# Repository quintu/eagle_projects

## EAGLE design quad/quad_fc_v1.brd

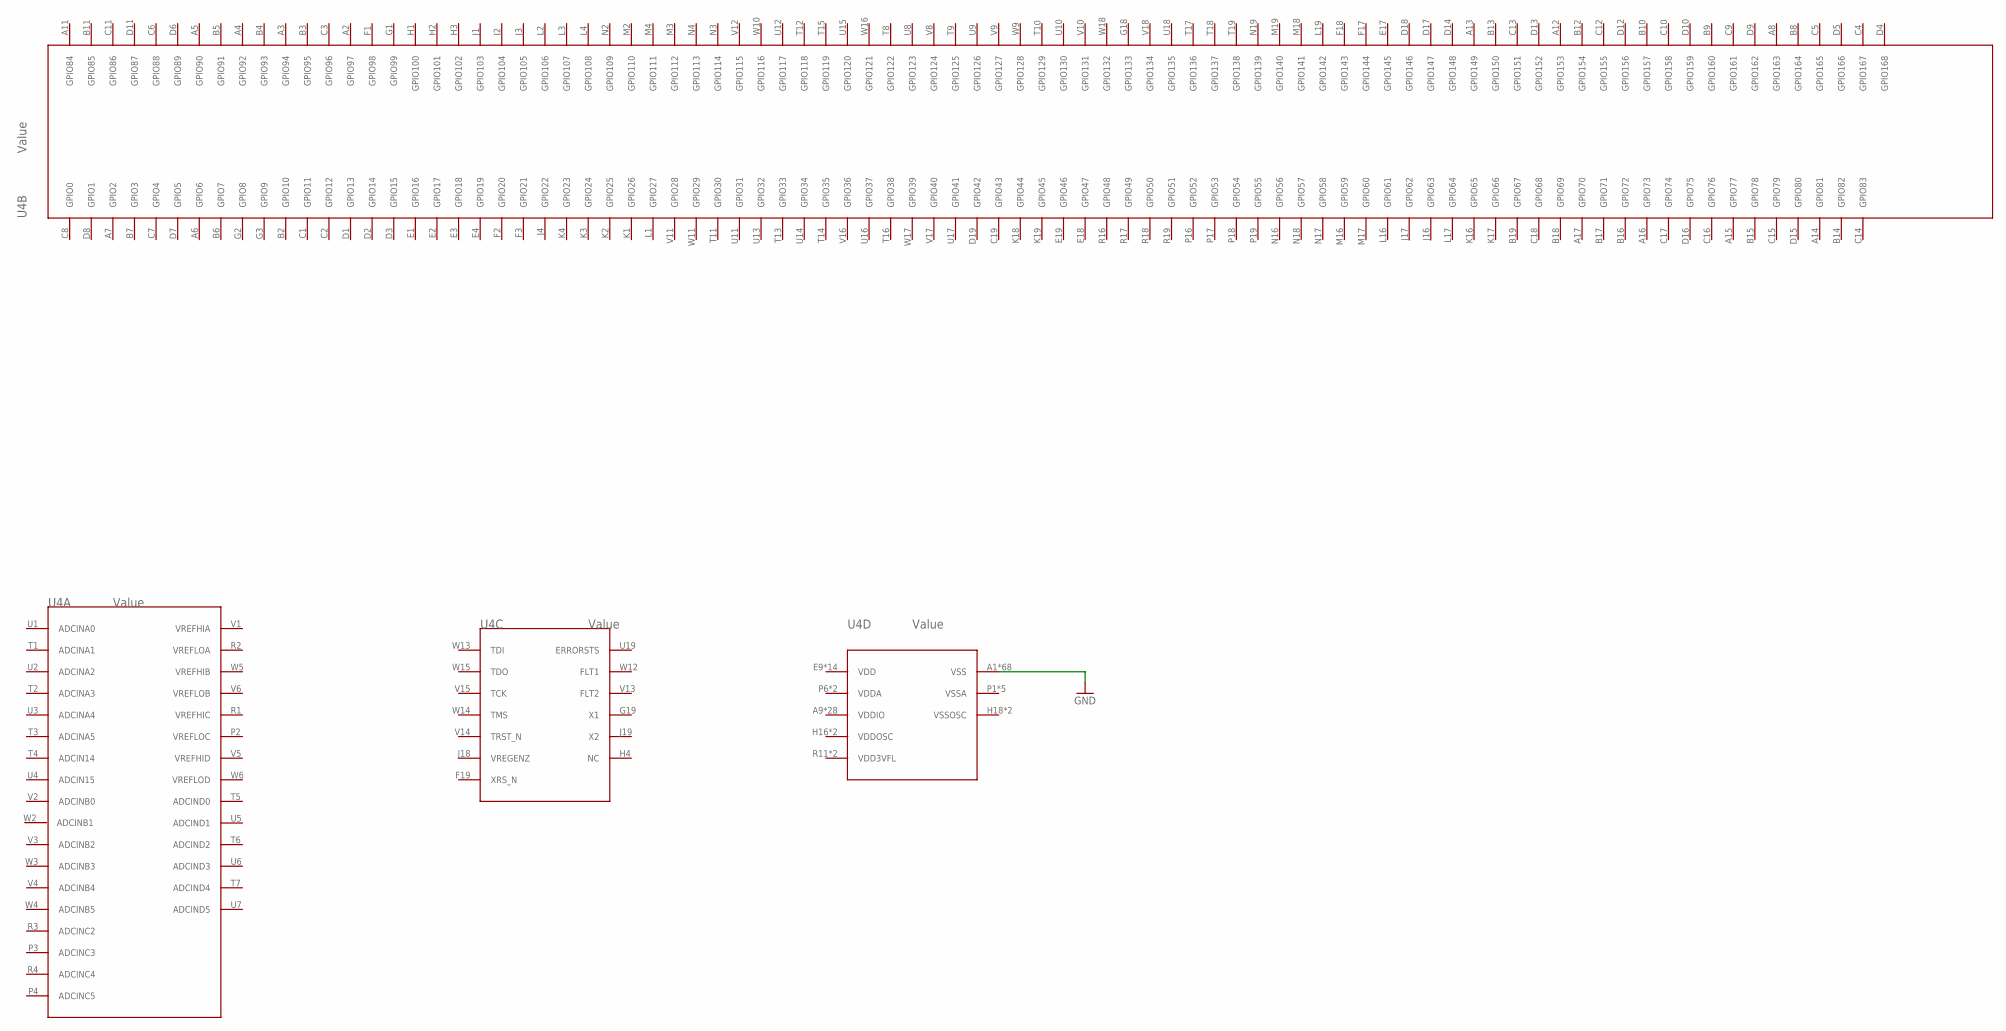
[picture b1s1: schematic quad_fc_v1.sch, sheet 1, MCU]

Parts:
U4: Value; ZWT0337A

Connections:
GND: U4.A1 (VSS), U4.A10 (VSS), U4.A19 (VSS), U4.E5 (VSS), U4.E6 (VSS), U4.E8 (VSS), U4.E12 (VSS), U4.E14 (VSS), U4.E15 (VSS), U4.F5 (VSS), U4.F6 (VSS), U4.F8 (VSS), U4.F12 (VSS), U4.F14 (VSS), U4.F15 (VSS), U4.G16 (VSS), U4.G17 (VSS), U4.H8 (VSS), U4.H9 (VSS), U4.H10 (VSS), U4.H11 (VSS), U4.H12 (VSS), U4.H14 (VSS), U4.H15 (VSS), U4.J5 (VSS), U4.J6 (VSS), U4.J8 (VSS), U4.J9 (VSS), U4.J10 (VSS), U4.J11 (VSS), U4.J12 (VSS), U4.K8 (VSS), U4.K9 (VSS), U4.K10 (VSS), U4.K11 (VSS), U4.K12 (VSS), U4.K14 (VSS), U4.K15 (VSS), U4.L5 (VSS), U4.L6 (VSS), U4.L8 (VSS), U4.L9 (VSS), U4.L10 (VSS), U4.L11 (VSS), U4.L12 (VSS), U4.L18 (VSS), U4.M8 (VSS), U4.M9 (VSS), U4.M10 (VSS), U4.M11 (VSS), U4.M12 (VSS), U4.M14 (VSS), U4.M15 (VSS), U4.N1 (VSS), U4.N5 (VSS), U4.N6 (VSS), U4.P7 (VSS), U4.P8 (VSS), U4.P11 (VSS), U4.P12 (VSS), U4.P14 (VSS), U4.P15 (VSS), U4.R7 (VSS), U4.R8 (VSS), U4.R14 (VSS), U4.R15 (VSS), U4.W7 (VSS), U4.W19 (VSS)
VDD: U4.E9 (VDD), U4.E11 (VDD), U4.F9 (VDD), U4.F11 (VDD), U4.G14 (VDD), U4.G15 (VDD), U4.J14 (VDD), U4.J15 (VDD), U4.K5 (VDD), U4.K6 (VDD), U4.P10 (VDD), U4.P13 (VDD), U4.R10 (VDD), U4.R13 (VDD)
VDD3VFL: U4.R11 (VDD3VFL), U4.R12 (VDD3VFL)
VDDA: U4.P6 (VDDA), U4.R6 (VDDA)
VDDIO: U4.A9 (VDDIO), U4.A18 (VDDIO), U4.B1 (VDDIO), U4.E7 (VDDIO), U4.E10 (VDDIO), U4.E13 (VDDIO), U4.E16 (VDDIO), U4.F4 (VDDIO), U4.F7 (VDDIO), U4.F10 (VDDIO), U4.F13 (VDDIO), U4.F16 (VDDIO), U4.G4 (VDDIO), U4.G5 (VDDIO), U4.G6 (VDDIO), U4.H5 (VDDIO), U4.H6 (VDDIO), U4.L14 (VDDIO), U4.L15 (VDDIO), U4.M1 (VDDIO), U4.M5 (VDDIO), U4.M6 (VDDIO), U4.N14 (VDDIO), U4.N15 (VDDIO), U4.P9 (VDDIO), U4.R9 (VDDIO), U4.V19 (VDDIO), U4.W8 (VDDIO)
VDDOSC: U4.H16 (VDDOSC), U4.H17 (VDDOSC)
VSSA: U4.P1 (VSSA), U4.P5 (VSSA), U4.R5 (VSSA), U4.V7 (VSSA), U4.W1 (VSSA)
VSSOSC: U4.H18 (VSSOSC), U4.H19 (VSSOSC)

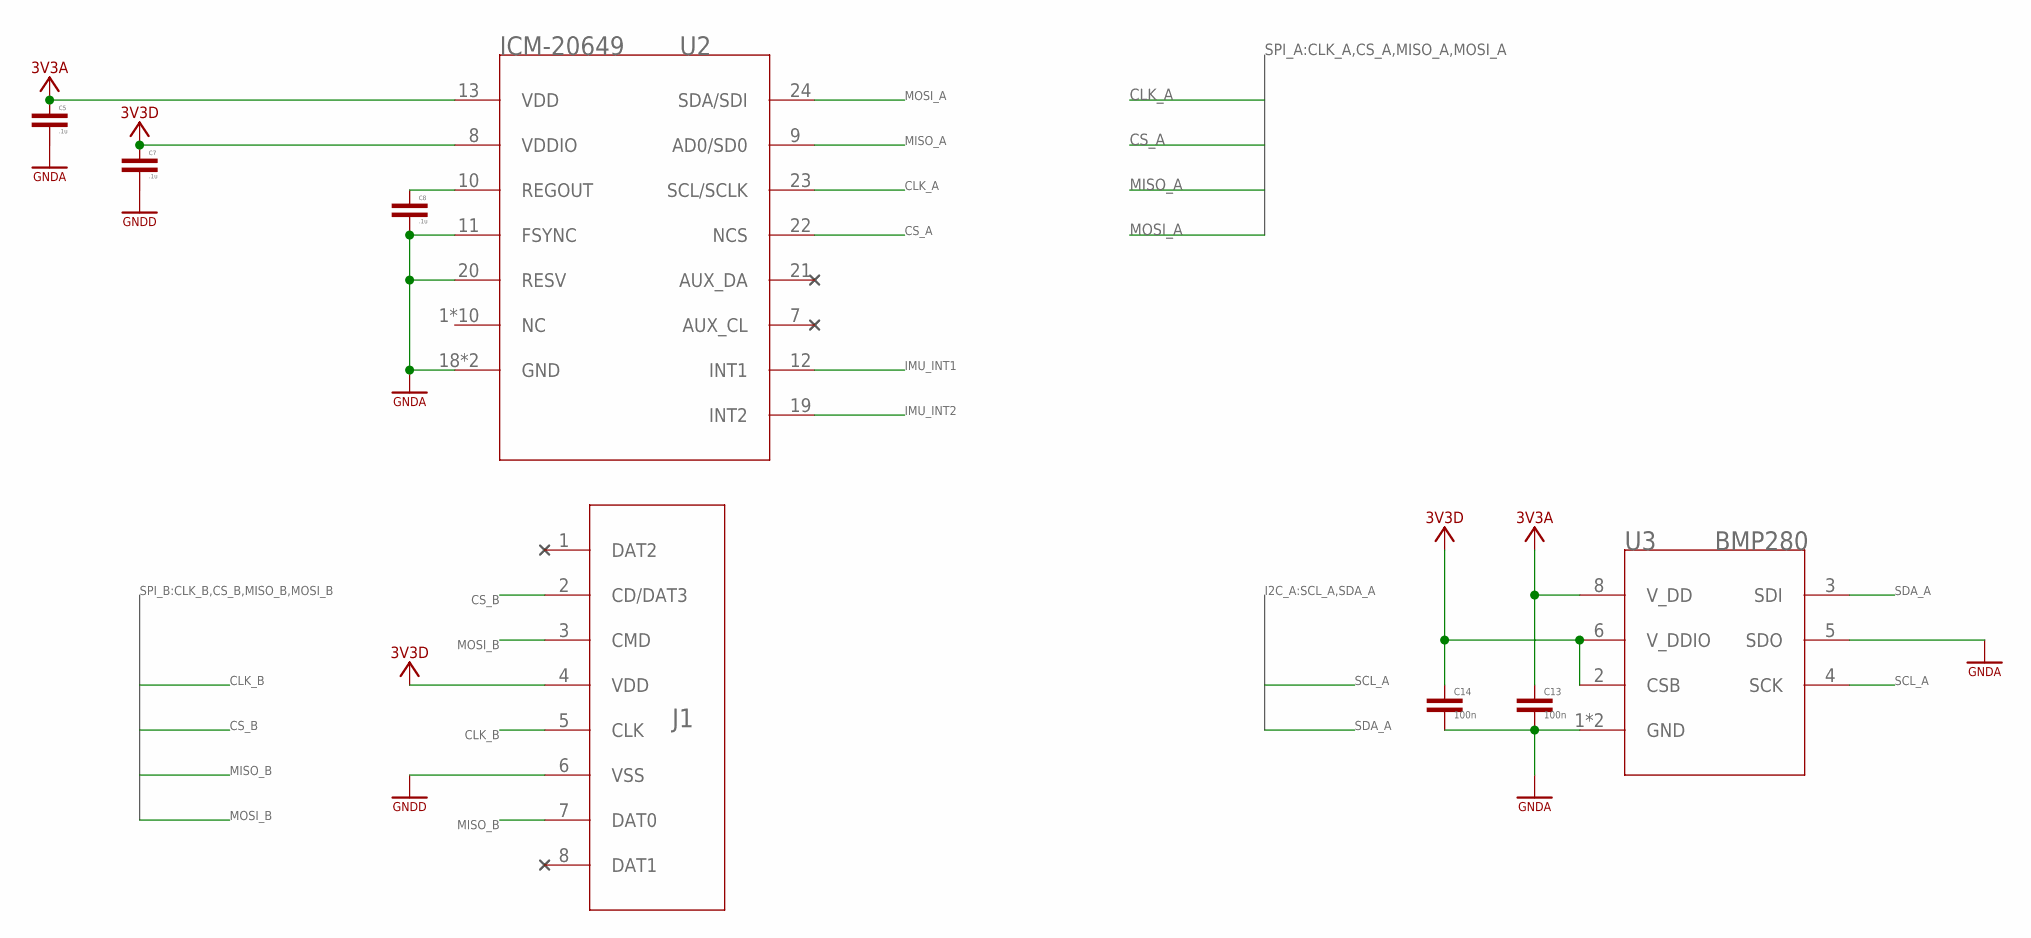
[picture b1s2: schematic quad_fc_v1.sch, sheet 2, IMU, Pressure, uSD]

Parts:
C5, C7, C8: .1u; C0805
C13, C14: 100n; C0603
J1: DM3CS-SF; CONN_3CS-SF
U2: ICM-20649; QFN24_3X3X0P9_IVS
U3: BMP280; LGA8_BMP280_BOS

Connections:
3V3A: C5.1, C13.1, U2.13 (VDD), U3.8 (V_DD); also elsewhere on the board
3V3D: C7.1, C14.1, J1.4 (VDD), U2.8 (VDDIO), U3.2 (CSB), U3.6 (V_DDIO); also elsewhere on the board
CLK_A: U2.23 (SCL/SCLK)
CLK_B: J1.5 (CLK)
CS_A: U2.22 (NCS)
CS_B: J1.2 (CD/DAT3)
GNDA: C5.2, C8.2, C13.2, C14.2, U2.11 (FSYNC), U2.18 (GND), U2.20 (RESV), U2.25 (GND), U3.1 (GND), U3.5 (SDO), U3.7 (GND); also elsewhere on the board
GNDD: C7.2, J1.6 (VSS)
IMU_INT1: U2.12 (INT1)
IMU_INT2: U2.19 (INT2)
MISO_A: U2.9 (AD0/SD0)
MISO_B: J1.7 (DAT0)
MOSI_A: U2.24 (SDA/SDI)
MOSI_B: J1.3 (CMD)
unnamed: C8.1, U2.10 (REGOUT)
SCL_A: U3.4 (SCK)
SDA_A: U3.3 (SDI)

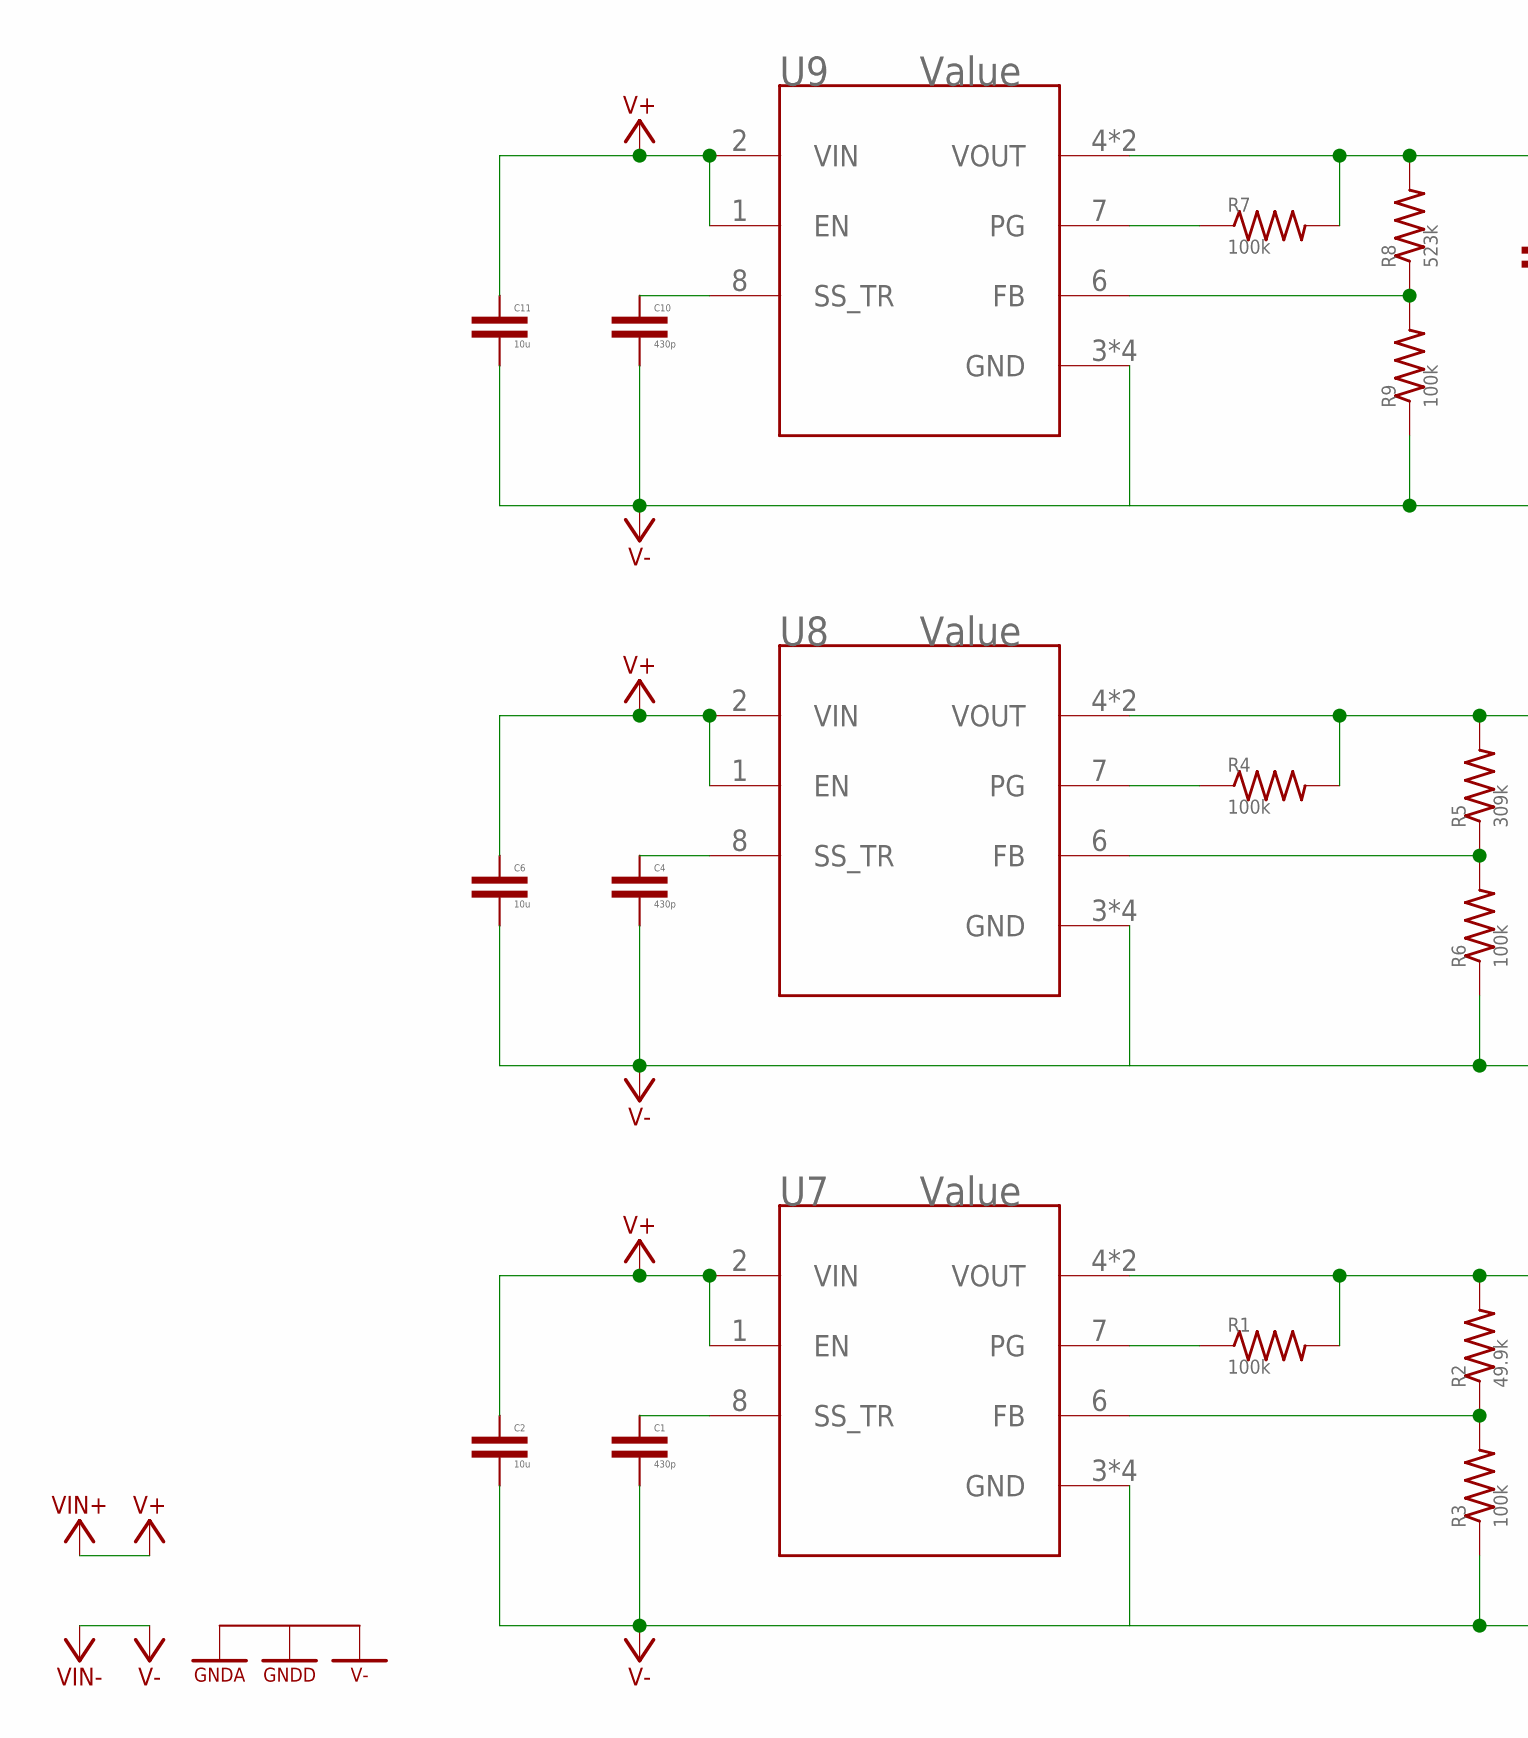
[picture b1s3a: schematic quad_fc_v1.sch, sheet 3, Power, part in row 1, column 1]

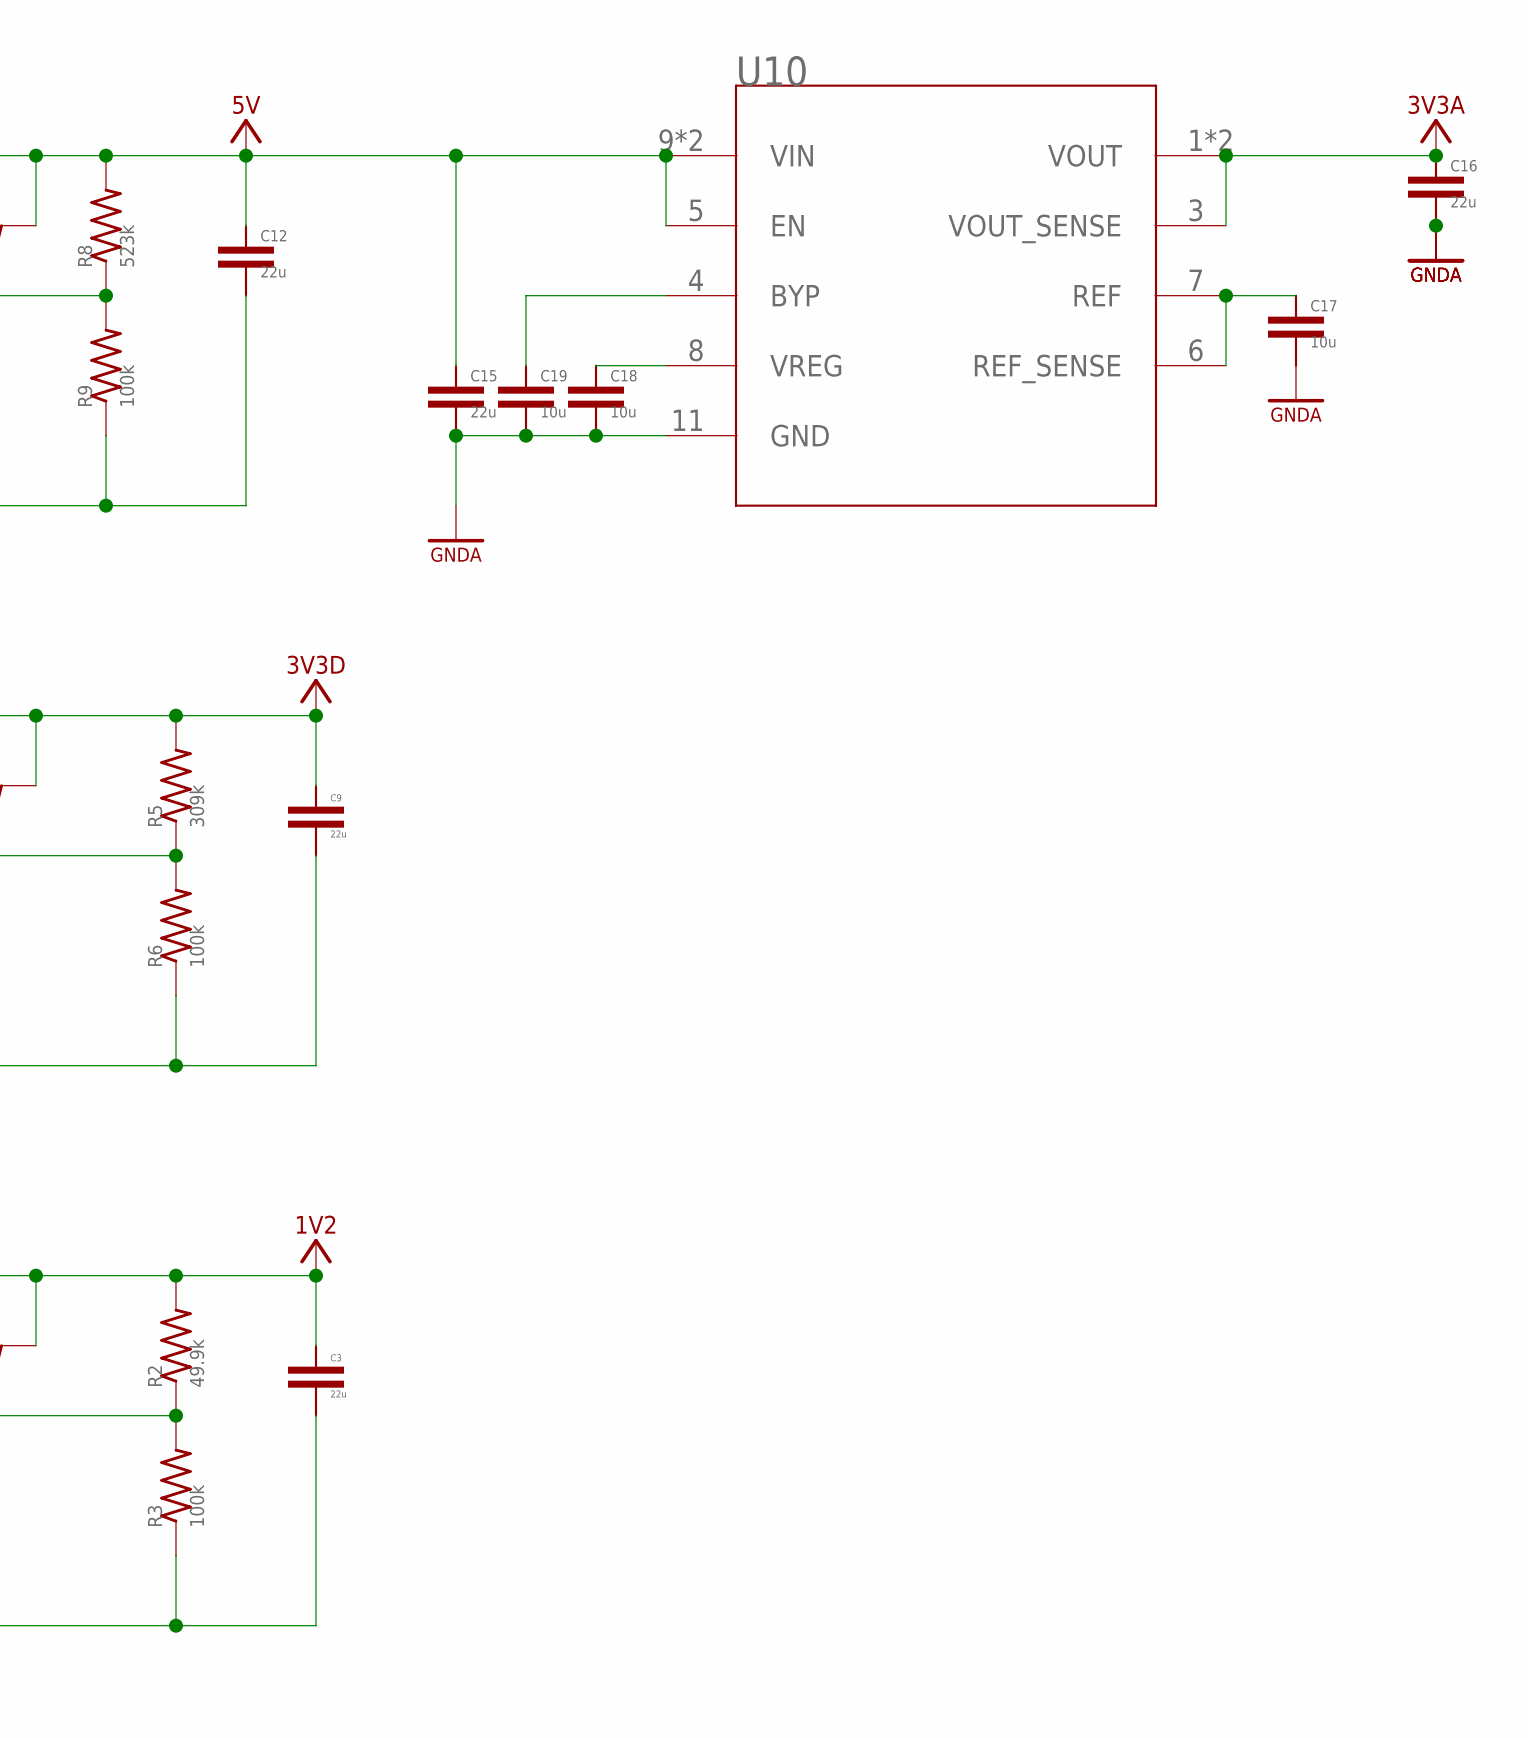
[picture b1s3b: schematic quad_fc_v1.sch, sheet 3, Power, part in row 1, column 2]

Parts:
C1, C4, C10: 430p; C0603
C2, C6, C11, C17, C18, C19: 10u; C0603
C3, C9, C12, C15, C16: 22u; C0805
R1, R3, R4, R6, R7, R9: 100k; R0603
R2: 49.9k; R0603
R5: 309k; R0603
R8: 523k; R0603
U7, U8, U9: Value; SIL0008D_SMD
U10: ADP7156ACPZ-3.3-R7CP_10_9_ADI-L; CP_10_9_ADI-L
U$1: VIN+; BAT_SOLDER_PAD
U$2: VIN-; BAT_SOLDER_PAD
U$6: STARGND

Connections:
1V2: C3.1, R1.2, R2.2, U7.4 (VOUT), U7.5 (VOUT)
3V3A: C16.1, U10.1 (VOUT), U10.2 (VOUT), U10.3 (VOUT_SENSE); also elsewhere on the board
3V3D: C9.1, R4.2, R5.2, U8.4 (VOUT), U8.5 (VOUT); also elsewhere on the board
5V: C12.1, C15.1, R7.2, R8.2, U9.4 (VOUT), U9.5 (VOUT), U10.5 (EN), U10.9 (VIN), U10.10 (VIN); also elsewhere on the board
GNDA: C15.2, C16.2, C17.2, C18.2, C19.2, U10.11 (GND); also elsewhere on the board
unnamed: R2.1, R3.2, U7.6 (FB)
unnamed: C17.1, U10.6 (REF_SENSE), U10.7 (REF)
unnamed: R1.1, U7.7 (PG)
unnamed: C1.1, U7.8 (SS_TR)
unnamed: U7.3 (GND), U7.9 (GND), U7.10 (GND), U7.11 (GND)
unnamed: C18.1, U10.8 (VREG)
unnamed: R5.1, R6.2, U8.6 (FB)
unnamed: C19.1, U10.4 (BYP)
unnamed: R4.1, U8.7 (PG)
unnamed: C4.1, U8.8 (SS_TR)
unnamed: U8.3 (GND), U8.9 (GND), U8.10 (GND), U8.11 (GND)
unnamed: R8.1, R9.2, U9.6 (FB)
unnamed: R7.1, U9.7 (PG)
unnamed: C10.1, U9.8 (SS_TR)
unnamed: U9.3 (GND), U9.9 (GND), U9.10 (GND), U9.11 (GND)
V+: C2.1, C6.1, C11.1, U7.1 (EN), U7.2 (VIN), U8.1 (EN), U8.2 (VIN), U9.1 (EN), U9.2 (VIN); also elsewhere on the board
V-: C1.2, C2.2, C3.2, C4.2, C6.2, C9.2, C10.2, C11.2, C12.2, R3.1, R6.1, R9.1; also elsewhere on the board
VIN+: U$1.V
VIN-: U$2.V

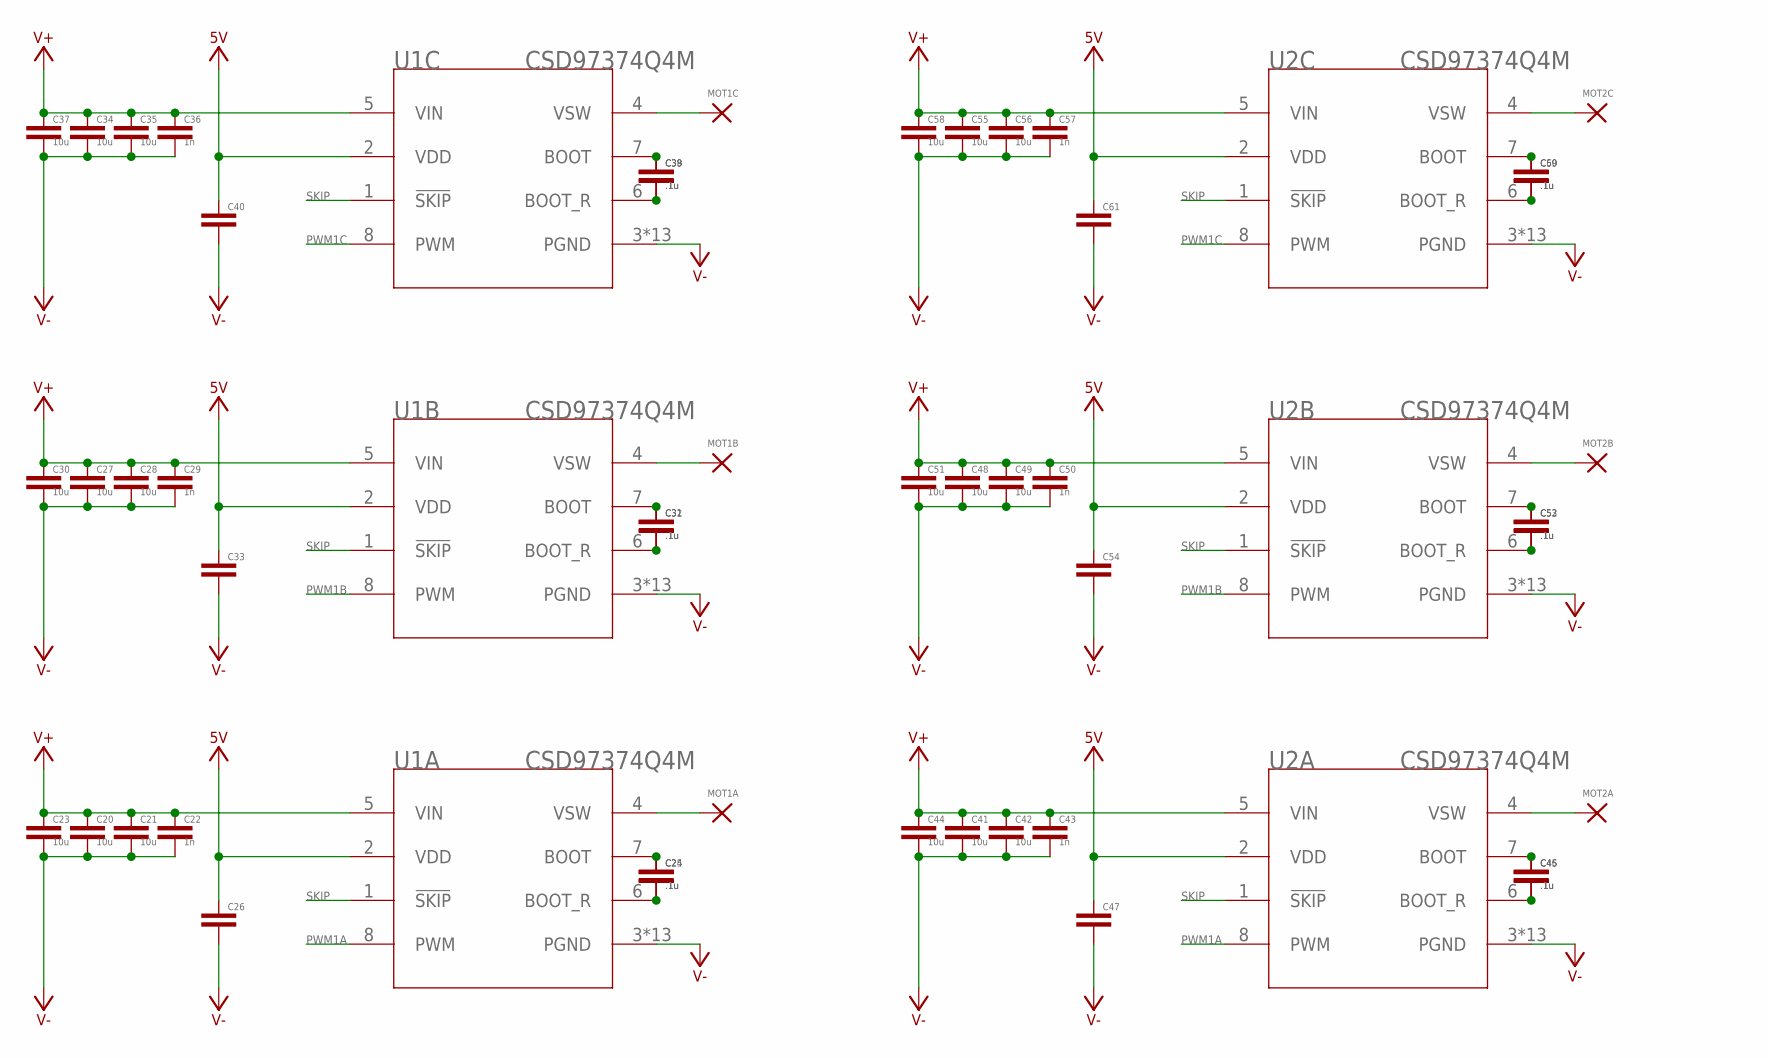
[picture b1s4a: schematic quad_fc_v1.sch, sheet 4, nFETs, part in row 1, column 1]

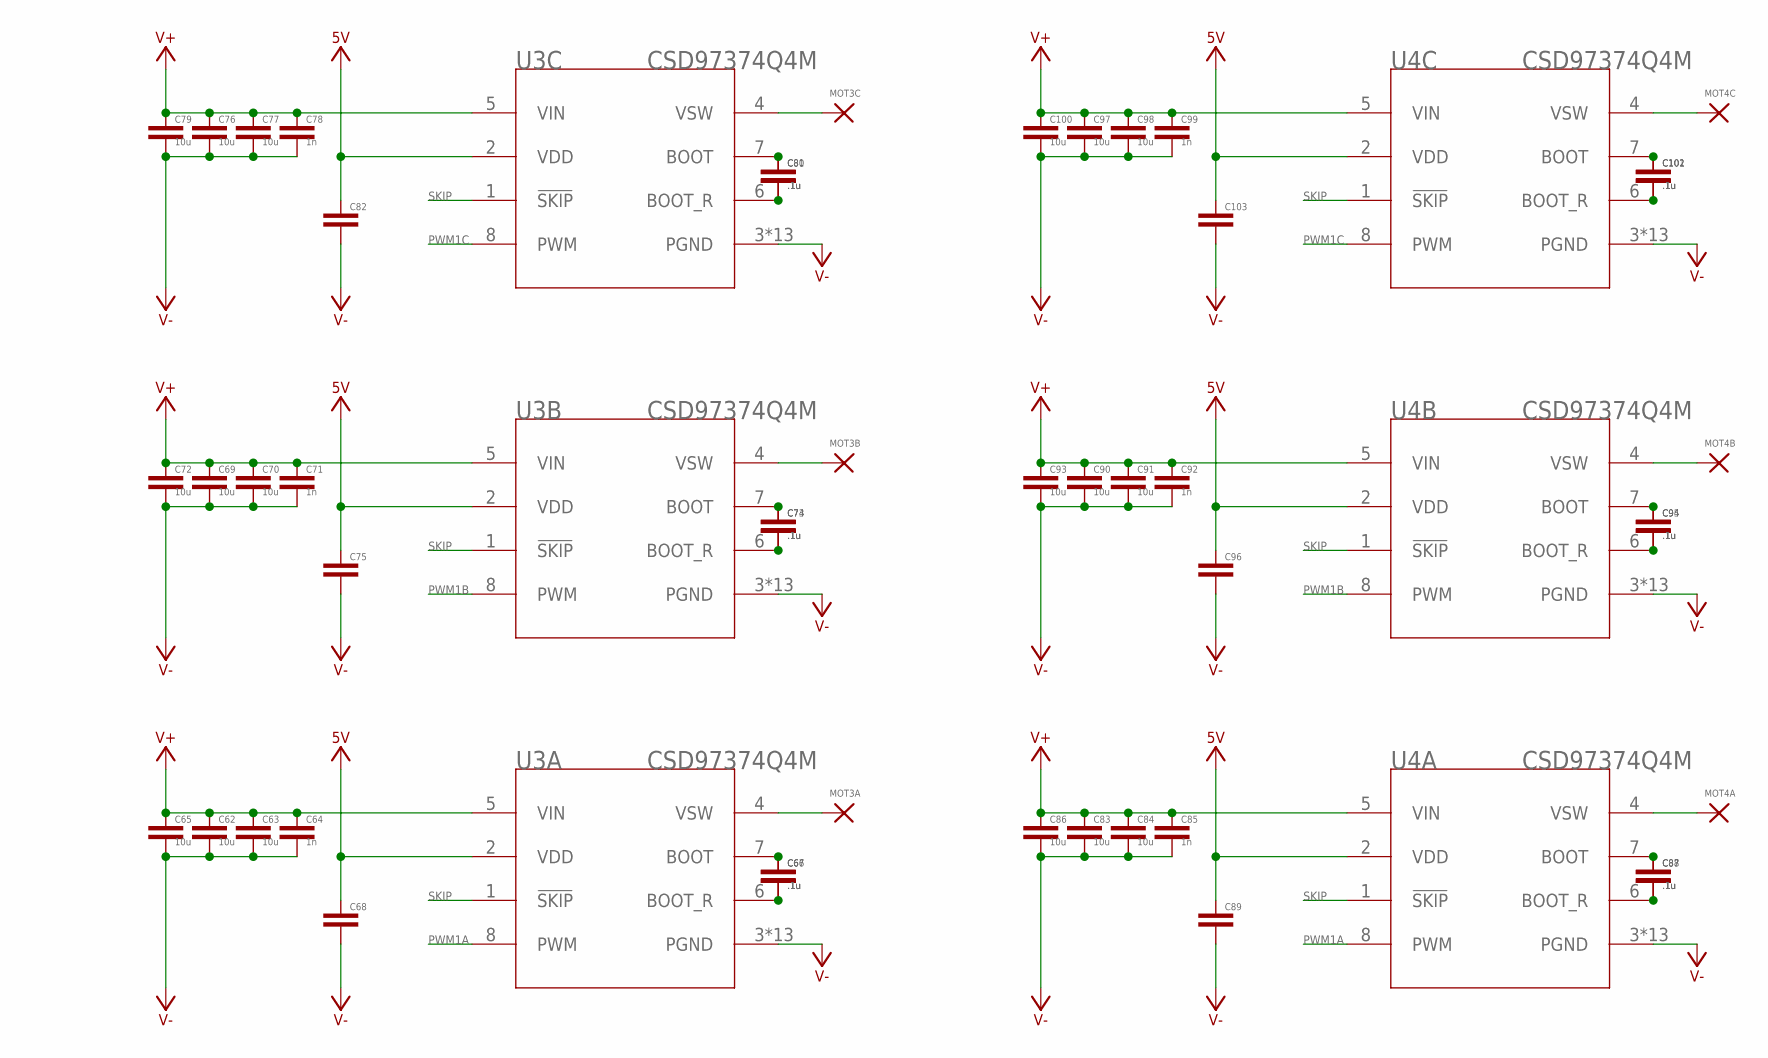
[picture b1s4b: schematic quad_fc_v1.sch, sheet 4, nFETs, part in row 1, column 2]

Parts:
C20, C21, C23, C27, C28, C30, C34, C35, C37, C41, C42, C44, C48, C49, C51, C55, C56, C58, C62, C63, C65, C69, C70, C72, C76, C77, C79, C83, C84, C86, C90, C91, C93, C97, C98, C100: 10u; C0603
C22, C29, C36, C43, C50, C57, C64, C71, C78, C85, C92, C99: 1n; C0603
C24, C25, C31, C32, C38, C39, C45, C46, C52, C53, C59, C60, C66, C67, C73, C74, C80, C81, C87, C88, C94, C95, C101, C102: .1u; C0603
C26, C33, C40, C47, C54, C61, C68, C75, C82, C89, C96, C103: C-EUC0603; C0603
MOT1A, MOT1B, MOT1C, MOT2A, MOT2B, MOT2C, MOT3A, MOT3B, MOT3C, MOT4A, MOT4B, MOT4C: MOT_SOLDER_PAD
U1A, U1B, U1C, U2A, U2B, U2C, U3A, U3B, U3C, U4A, U4B, U4C: CSD97374Q4M; DPC8

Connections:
5V: C26.1, C33.1, C40.1, C47.1, C54.1, C61.1, C68.1, C75.1, C82.1, C89.1, C96.1, C103.1, U1A.2 (VDD), U1B.2 (VDD), U1C.2 (VDD), U2A.2 (VDD), U2B.2 (VDD), U2C.2 (VDD), U3A.2 (VDD), U3B.2 (VDD), U3C.2 (VDD), U4A.2 (VDD), U4B.2 (VDD), U4C.2 (VDD); also elsewhere on the board
unnamed: C24.1, C25.1, U1A.7 (BOOT)
unnamed: C24.2, C25.2, U1A.6 (BOOT_R)
unnamed: MOT1A.1, U1A.4 (VSW)
unnamed: C31.1, C32.1, U1B.7 (BOOT)
unnamed: C31.2, C32.2, U1B.6 (BOOT_R)
unnamed: MOT1B.1, U1B.4 (VSW)
unnamed: C38.1, C39.1, U1C.7 (BOOT)
unnamed: C38.2, C39.2, U1C.6 (BOOT_R)
unnamed: MOT1C.1, U1C.4 (VSW)
unnamed: C45.1, C46.1, U2A.7 (BOOT)
unnamed: C45.2, C46.2, U2A.6 (BOOT_R)
unnamed: MOT2A.1, U2A.4 (VSW)
unnamed: C52.1, C53.1, U2B.7 (BOOT)
unnamed: C52.2, C53.2, U2B.6 (BOOT_R)
unnamed: MOT2B.1, U2B.4 (VSW)
unnamed: C59.1, C60.1, U2C.7 (BOOT)
unnamed: C59.2, C60.2, U2C.6 (BOOT_R)
unnamed: MOT2C.1, U2C.4 (VSW)
unnamed: C66.1, C67.1, U3A.7 (BOOT)
unnamed: C66.2, C67.2, U3A.6 (BOOT_R)
unnamed: MOT3A.1, U3A.4 (VSW)
unnamed: C73.1, C74.1, U3B.7 (BOOT)
unnamed: C73.2, C74.2, U3B.6 (BOOT_R)
unnamed: MOT3B.1, U3B.4 (VSW)
unnamed: C80.1, C81.1, U3C.7 (BOOT)
unnamed: C80.2, C81.2, U3C.6 (BOOT_R)
unnamed: MOT3C.1, U3C.4 (VSW)
unnamed: C87.1, C88.1, U4A.7 (BOOT)
unnamed: C87.2, C88.2, U4A.6 (BOOT_R)
unnamed: MOT4A.1, U4A.4 (VSW)
unnamed: C94.1, C95.1, U4B.7 (BOOT)
unnamed: C94.2, C95.2, U4B.6 (BOOT_R)
unnamed: MOT4B.1, U4B.4 (VSW)
unnamed: C101.1, C102.1, U4C.7 (BOOT)
unnamed: C101.2, C102.2, U4C.6 (BOOT_R)
unnamed: MOT4C.1, U4C.4 (VSW)
PWM1A: U1A.8 (PWM), U2A.8 (PWM), U3A.8 (PWM), U4A.8 (PWM)
PWM1B: U1B.8 (PWM), U2B.8 (PWM), U3B.8 (PWM), U4B.8 (PWM)
PWM1C: U1C.8 (PWM), U2C.8 (PWM), U3C.8 (PWM), U4C.8 (PWM)
SKIP: U1A.1 (!SKIP), U1B.1 (!SKIP), U1C.1 (!SKIP), U2A.1 (!SKIP), U2B.1 (!SKIP), U2C.1 (!SKIP), U3A.1 (!SKIP), U3B.1 (!SKIP), U3C.1 (!SKIP), U4A.1 (!SKIP), U4B.1 (!SKIP), U4C.1 (!SKIP)
V+: C20.1, C21.1, C22.1, C23.1, C27.1, C28.1, C29.1, C30.1, C34.1, C35.1, C36.1, C37.1, C41.1, C42.1, C43.1, C44.1, C48.1, C49.1, C50.1, C51.1, C55.1, C56.1, C57.1, C58.1, C62.1, C63.1, C64.1, C65.1, C69.1, C70.1, C71.1, C72.1, C76.1, C77.1, C78.1, C79.1, C83.1, C84.1, C85.1, C86.1, C90.1, C91.1, C92.1, C93.1, C97.1, C98.1, C99.1, C100.1, U1A.5 (VIN), U1B.5 (VIN), U1C.5 (VIN), U2A.5 (VIN), U2B.5 (VIN), U2C.5 (VIN), U3A.5 (VIN), U3B.5 (VIN), U3C.5 (VIN), U4A.5 (VIN), U4B.5 (VIN), U4C.5 (VIN); also elsewhere on the board
V-: C20.2, C21.2, C22.2, C23.2, C26.2, C27.2, C28.2, C29.2, C30.2, C33.2, C34.2, C35.2, C36.2, C37.2, C40.2, C41.2, C42.2, C43.2, C44.2, C47.2, C48.2, C49.2, C50.2, C51.2, C54.2, C55.2, C56.2, C57.2, C58.2, C61.2, C62.2, C63.2, C64.2, C65.2, C68.2, C69.2, C70.2, C71.2, C72.2, C75.2, C76.2, C77.2, C78.2, C79.2, C82.2, C83.2, C84.2, C85.2, C86.2, C89.2, C90.2, C91.2, C92.2, C93.2, C96.2, C97.2, C98.2, C99.2, C100.2, C103.2, U1A.3 (PGND), U1A.9 (PGND), U1A.V10 (PGND), U1A.V11 (PGND), U1A.V12 (PGND), U1A.V13 (PGND), U1A.V14 (PGND), U1A.V15 (PGND), U1A.V16 (PGND), U1A.V17 (PGND), U1A.V18 (PGND), U1A.V19 (PGND), U1A.V20 (PGND), U1B.3 (PGND), U1B.9 (PGND), U1B.V10 (PGND), U1B.V11 (PGND), U1B.V12 (PGND), U1B.V13 (PGND), U1B.V14 (PGND), U1B.V15 (PGND), U1B.V16 (PGND), U1B.V17 (PGND), U1B.V18 (PGND), U1B.V19 (PGND), U1B.V20 (PGND), U1C.3 (PGND), U1C.9 (PGND), U1C.V10 (PGND), U1C.V11 (PGND), U1C.V12 (PGND), U1C.V13 (PGND), U1C.V14 (PGND), U1C.V15 (PGND), U1C.V16 (PGND), U1C.V17 (PGND), U1C.V18 (PGND), U1C.V19 (PGND), U1C.V20 (PGND), U2A.3 (PGND), U2A.9 (PGND), U2A.V10 (PGND), U2A.V11 (PGND), U2A.V12 (PGND), U2A.V13 (PGND), U2A.V14 (PGND), U2A.V15 (PGND), U2A.V16 (PGND), U2A.V17 (PGND), U2A.V18 (PGND), U2A.V19 (PGND), U2A.V20 (PGND), U2B.3 (PGND), U2B.9 (PGND), U2B.V10 (PGND), U2B.V11 (PGND), U2B.V12 (PGND), U2B.V13 (PGND), U2B.V14 (PGND), U2B.V15 (PGND), U2B.V16 (PGND), U2B.V17 (PGND), U2B.V18 (PGND), U2B.V19 (PGND), U2B.V20 (PGND), U2C.3 (PGND), U2C.9 (PGND), U2C.V10 (PGND), U2C.V11 (PGND), U2C.V12 (PGND), U2C.V13 (PGND), U2C.V14 (PGND), U2C.V15 (PGND), U2C.V16 (PGND), U2C.V17 (PGND), U2C.V18 (PGND), U2C.V19 (PGND), U2C.V20 (PGND), U3A.3 (PGND), U3A.9 (PGND), U3A.V10 (PGND), U3A.V11 (PGND), U3A.V12 (PGND), U3A.V13 (PGND), U3A.V14 (PGND), U3A.V15 (PGND), U3A.V16 (PGND), U3A.V17 (PGND), U3A.V18 (PGND), U3A.V19 (PGND), U3A.V20 (PGND), U3B.3 (PGND), U3B.9 (PGND), U3B.V10 (PGND), U3B.V11 (PGND), U3B.V12 (PGND), U3B.V13 (PGND), U3B.V14 (PGND), U3B.V15 (PGND), U3B.V16 (PGND), U3B.V17 (PGND), U3B.V18 (PGND), U3B.V19 (PGND), U3B.V20 (PGND), U3C.3 (PGND), U3C.9 (PGND), U3C.V10 (PGND), U3C.V11 (PGND), U3C.V12 (PGND), U3C.V13 (PGND), U3C.V14 (PGND), U3C.V15 (PGND), U3C.V16 (PGND), U3C.V17 (PGND), U3C.V18 (PGND), U3C.V19 (PGND), U3C.V20 (PGND), U4A.3 (PGND), U4A.9 (PGND), U4A.V10 (PGND), U4A.V11 (PGND), U4A.V12 (PGND), U4A.V13 (PGND), U4A.V14 (PGND), U4A.V15 (PGND), U4A.V16 (PGND), U4A.V17 (PGND), U4A.V18 (PGND), U4A.V19 (PGND), U4A.V20 (PGND), U4B.3 (PGND), U4B.9 (PGND), U4B.V10 (PGND), U4B.V11 (PGND), U4B.V12 (PGND), U4B.V13 (PGND), U4B.V14 (PGND), U4B.V15 (PGND), U4B.V16 (PGND), U4B.V17 (PGND), U4B.V18 (PGND), U4B.V19 (PGND), U4B.V20 (PGND), U4C.3 (PGND), U4C.9 (PGND), U4C.V10 (PGND), U4C.V11 (PGND), U4C.V12 (PGND), U4C.V13 (PGND), U4C.V14 (PGND), U4C.V15 (PGND), U4C.V16 (PGND), U4C.V17 (PGND), U4C.V18 (PGND), U4C.V19 (PGND), U4C.V20 (PGND); also elsewhere on the board

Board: 8 copper layers, 147 parts (0 on the bottom side), 72 nets, no tracks yet.

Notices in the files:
parts and their libraries:
COPYRIGHT: Copyright (C) 2018 Accelerated Designs. All rights reserved
